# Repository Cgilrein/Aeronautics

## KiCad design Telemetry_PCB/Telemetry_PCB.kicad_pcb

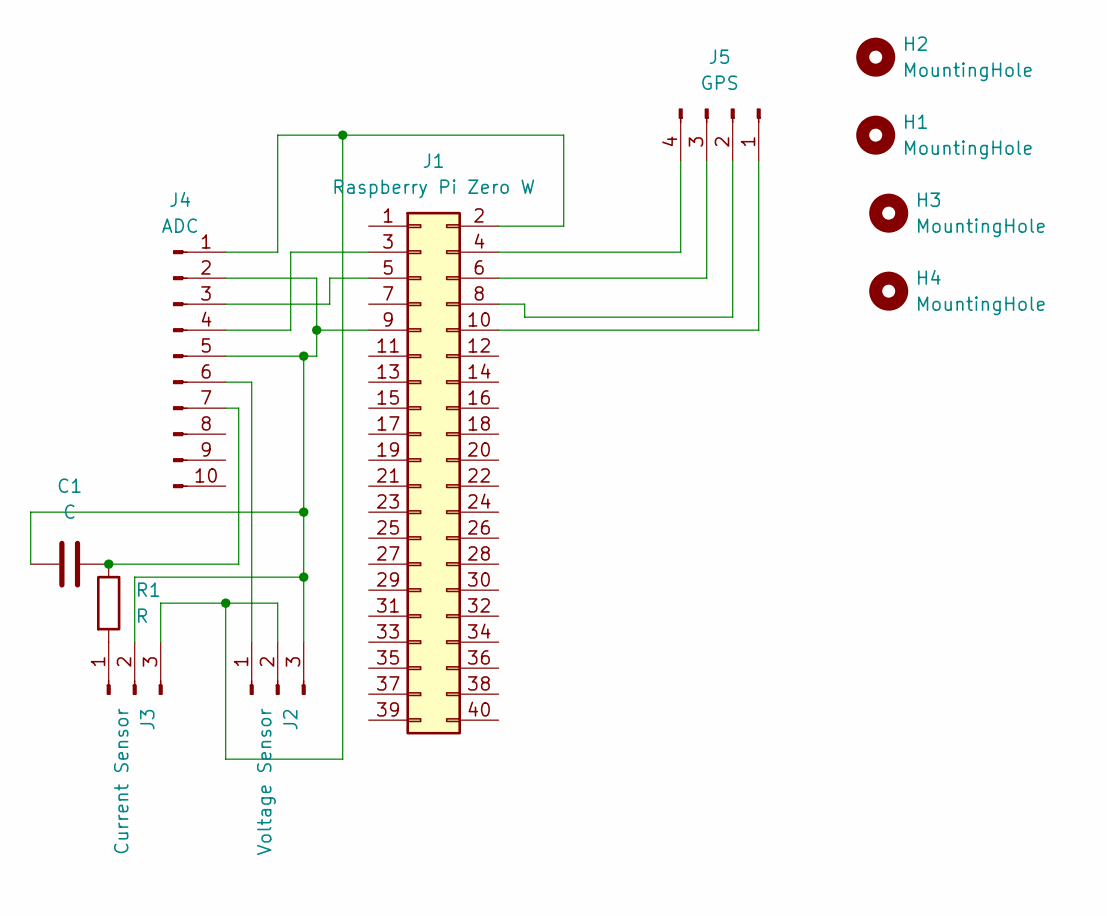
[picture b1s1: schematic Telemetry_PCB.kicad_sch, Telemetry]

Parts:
C1: C; C_Disc_D5.1mm_W3.2mm_P5.00mm
H1, H2, H3, H4: MountingHole; MountingHole_3.5mm
J1: Raspberry Pi Zero W; PinHeader_2x20_P2.54mm_Vertical
J2: Voltage Sensor; PinHeader_1x03_P2.54mm_Vertical
J3: Current Sensor; PinHeader_1x03_P2.54mm_Vertical
J4: ADC; PinHeader_1x10_P2.54mm_Vertical
J5: GPS; PinHeader_1x04_P2.54mm_Vertical
R1: R; R_Axial_DIN0207_L6.3mm_D2.5mm_P2.54mm_Vertical

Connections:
unnamed: J1.2, J2.2, J3.3, J4.1
unnamed: J1.3, J4.4
unnamed: J1.4, J5.4
unnamed: J1.5, J4.3
unnamed: J1.6, J5.3
unnamed: J1.8, J5.2
unnamed: C1.1, J1.9, J2.3, J3.2, J4.2, J4.5
unnamed: J1.10, J5.1
unnamed: J2.1, J4.6
unnamed: J3.1, R1.2
unnamed: C1.2, J4.7, R1.1

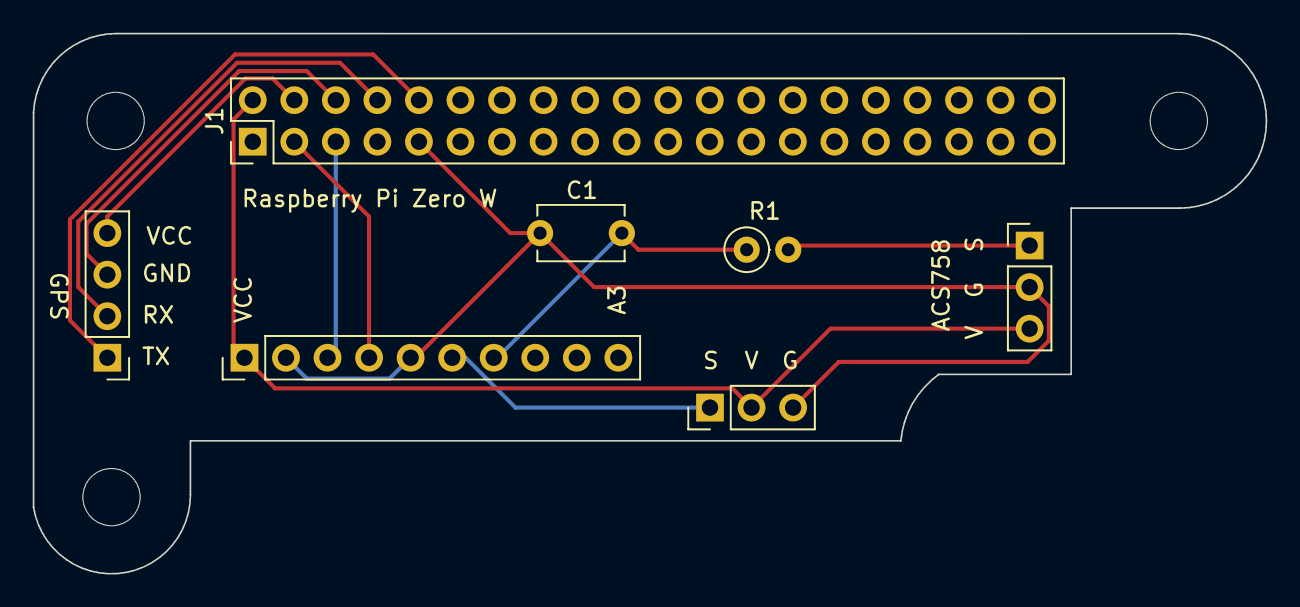
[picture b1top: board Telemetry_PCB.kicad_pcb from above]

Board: 2 copper layers, 75.4 x 33.0 mm, 10 parts (0 on the bottom side), 11 nets.

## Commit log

2023-11-30 Adding Wiring Schematics
2023-11-30 Orginization
2023-12-05 Edited test files to work with ADC (ADS1115)
2023-12-05 gps_testing
2023-12-16 Simple Bug Fix
2023-12-16 Fixed sensor reading
2024-01-18 Updated telemetry script
2024-01-18 Work Please
2024-01-18 Data fixing
2024-01-18 Attempting to fix timing
2024-02-06 Added way to calibrate current sensor
2024-02-08 Added power calculations and GPS parsing
2024-02-08 Updated schematic of full system
2024-02-08 Updated amp digital value
2024-02-11 Create avg_coordinates
    modified telemetry.py code to collect latitude and longitude data for one minute and then return the averages of those values
2024-02-11 Create GPS_accuracy
    calculates the distance between two coordinates and then compares it to the actual distance obtained from Google Maps to assess the accuracy of the GPS data
2024-02-13 Create accurate_time_telemetry_updated.py
    modified the accurate_time_telemetry.py script to return the averaged latitude and longitude data every minute for the duration of the runtime
2024-02-13 Cleaning Repository
2024-02-13 Organized
2024-02-13 data.txt test cases added
2024-02-14 Changed GPS formatted
2024-02-15 Fixed
2024-02-20 Create telemetry_updated
    fixed the averaging function and velocity graphing function
2024-02-20 Rename telemetry_updated to telemetry_updated.py
2024-02-20 Rename telemetry.py to telemetry_old.py
2024-02-20 Fixed current sensor zeroing
2024-02-20 Rename graphing.py to graphing_old.py
2024-02-20 Rename telemetry_updated.py to graphing.py
2024-02-20 Rename telemetry_old.py to telemetry.py
2024-02-20 Finally
2024-02-28 RAspberry pi
2024-02-29 Added threading to prevent gps bottleneck
2024-03-01 Added sample data files
2024-03-06 COCK
2024-03-06 Fixed GPS timing error
2024-03-06 More timing fixes
2024-03-07 this is dumb
2024-03-07 Added encrypting of github auth tokens
2024-03-10 Updated PCB Footprints
2024-03-12 Adding email system
2024-03-28 Added Status LED
2024-03-28 Added cleanup
2024-04-02 Personal Access Token
2024-04-02 new key
2024-04-02 token
2024-04-02 First Testing Data
2024-04-02 Need to fix plotting
2024-04-04 Added Deprecated
2024-04-04 Final Telemetry
2024-04-04 Final Changes
2024-04-15 Data
